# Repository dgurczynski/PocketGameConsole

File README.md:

# PocketGameConsole (ESP32-C3)

Przenośna mini-konsola oparta na układzie **ESP32-C3** z wyświetlaczem OLED 0.96". 

## O projekcie
To mój **pierwszy w życiu projekt PCB**, wykonany w całości w programie KiCad. Skupiłem się w nim na:
* Sprzętowym debouncingu przycisków (filtr RC).
* Czytelnym opisie warstw (Silkscreen) i estetyce logotypu.
* Bezpiecznym zasilaniu bateryjnym (dioda Schottky'ego).

## Zawartość repozytorium
* **[Software](src/):** Kod źródłowy C++ (PlatformIO).
* **[Schemat PDF](hardware/PocketGameConsole.pdf):** Pełna dokumentacja ideowa.
* **[Gerber ZIP](hardware/gerbers/PocketGameConsole_Gerbers.zip):** Pliki gotowe do zamówienia w fabryce.
* **[Projekt KiCad](hardware/pcb_project/):** Pliki źródłowe płytki.

### Podgląd 3D

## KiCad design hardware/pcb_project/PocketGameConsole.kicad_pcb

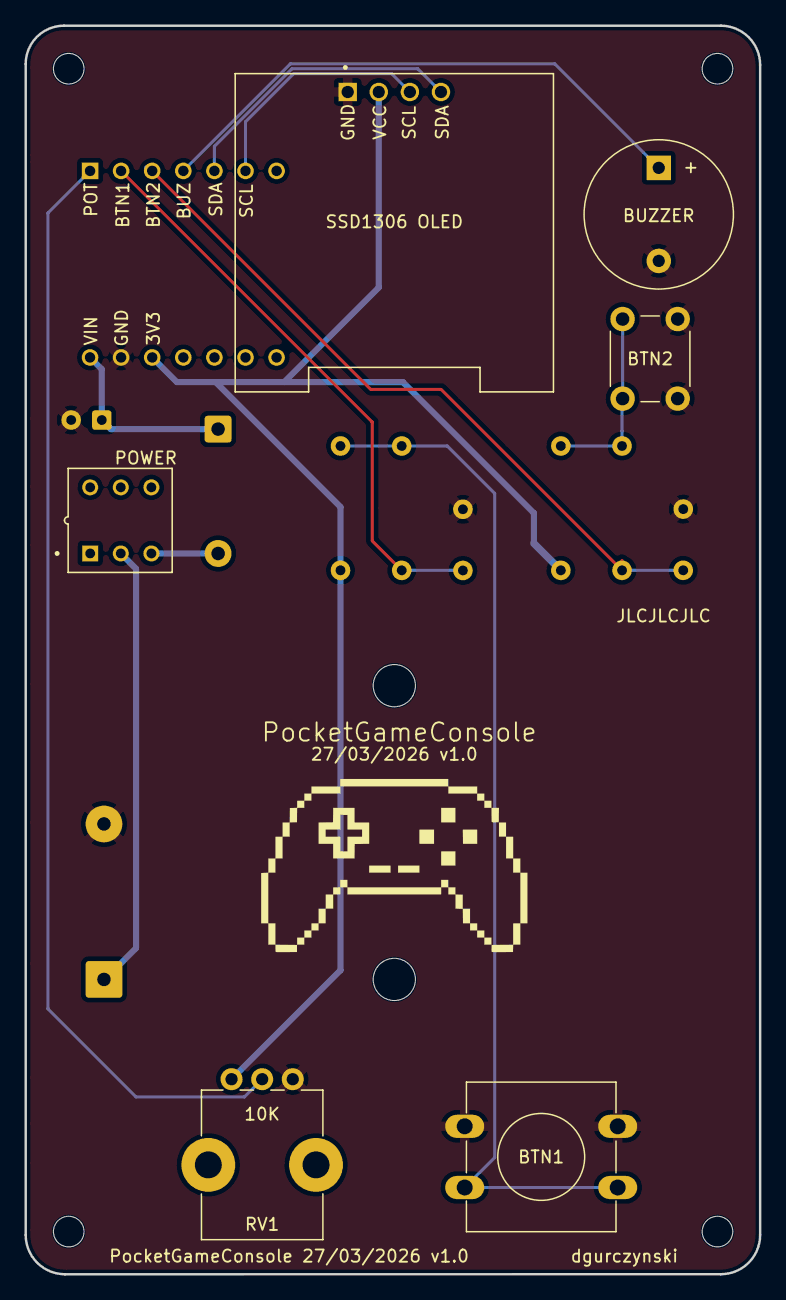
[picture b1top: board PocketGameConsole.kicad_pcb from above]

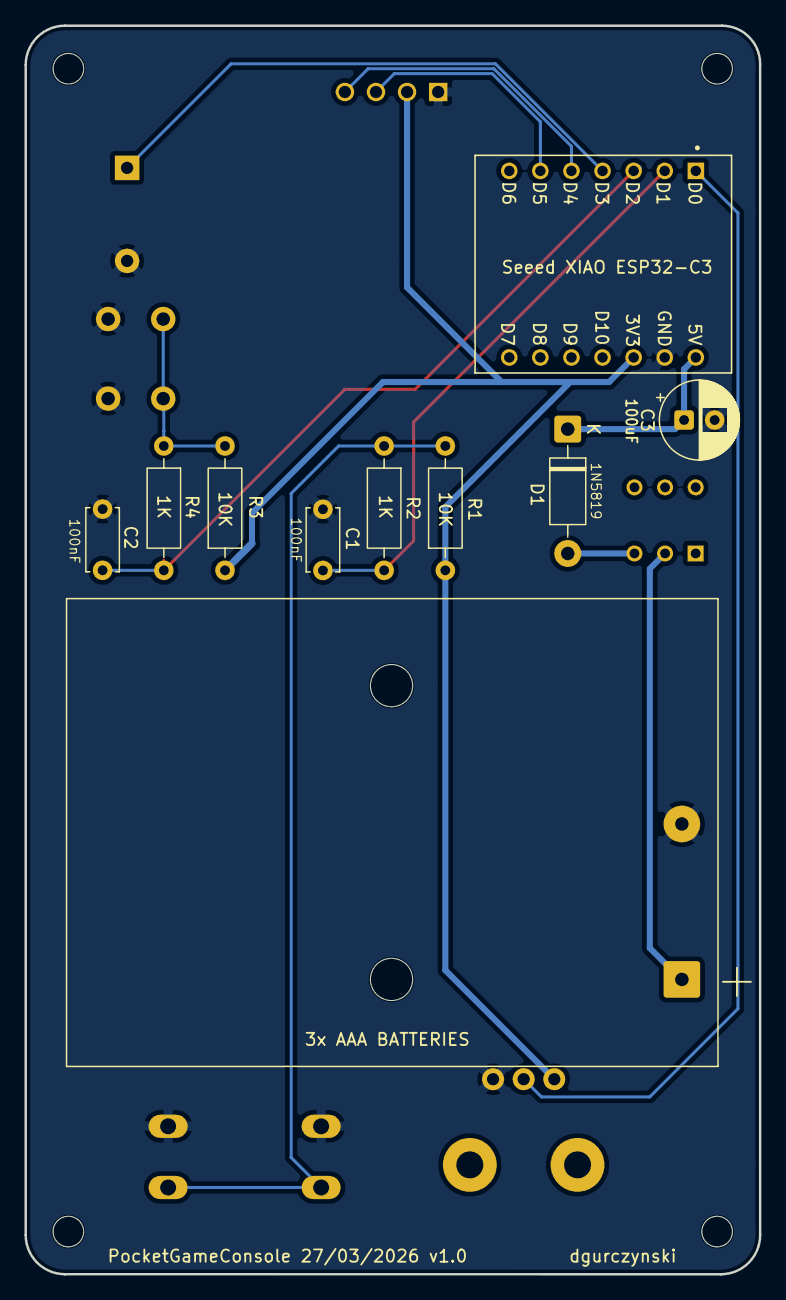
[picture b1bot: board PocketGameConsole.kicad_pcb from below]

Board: 4 copper layers, 60.0 x 102.0 mm, 16 parts (10 on the bottom side), 13 nets.

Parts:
1N5819: 1N5819; D_DO-41_SOD81_P10.16mm_Horizontal
3x AAA BATTERIES: 4.5V; BatteryHolder_Keystone_2479_3xAAA
100nF, 100nF#2: 100nF; C_Disc_D5.0mm_W2.5mm_P5.00mm
BZ1: BUZZER; Buzzer_12x9.5RM7.6
C3: 100uF; CP_Radial_D6.3mm_P2.50mm
R1, R3: 10K; R_Axial_DIN0207_L6.3mm_D2.5mm_P10.16mm_Horizontal
R2, R4: 1K; R_Axial_DIN0207_L6.3mm_D2.5mm_P10.16mm_Horizontal
RV1: 10K; Potentiometer_Bourns_PTV09A-1_Single_Vertical
S1: TL2201EEYA; SW_TL2201EEYA
SSD1306 0.96 OLED: DM-OLED096-636; MODULE_DM-OLED096-636
SW1: SW_Push; SW_PUSH-12mm
SW3: POWER; SW_PUSH_6mm
U1: XIAO-ESP32-C3-DIP; MODULE_XIAO_ESP32C3

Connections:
+3V3: R1.1, R3.1, RV1.1, SSD1306 0.96 OLED.2 (VCC_IN), U1.12 (3V3)
BTN1: 100nF#2.1, R2.2, U1.2 (GPIO3_A1_D1)
BTN2: 100nF.1, R4.2, U1.3 (GPIO4_A2_D2)
BUZ: BZ1.1 (+), U1.4 (GPIO5_A3_D3)
GND: 3x AAA BATTERIES.2 (-), 100nF.2, 100nF#2.2, BZ1.2 (-), C3.2, RV1.3, SSD1306 0.96 OLED.1 (GND), SW1.1, SW3.1, U1.13 (GND)
unnamed: 3x AAA BATTERIES.1 (+), S1.2
unnamed: 1N5819.2 (A), S1.3
unnamed: R1.2, R2.1, SW1.2
unnamed: R3.2, R4.1, SW3.2
POT: RV1.2, U1.1 (GPIO2_A0_D0)
SCL: SSD1306 0.96 OLED.3 (SCL), U1.6 (GPIO7_D5_SCL)
SDA: SSD1306 0.96 OLED.4 (SDA), U1.5 (GPIO6_D4_SDA)
VCC_BAT: 1N5819.1 (K), C3.1, U1.14 (VBUS)

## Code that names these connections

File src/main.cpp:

#include <Arduino.h>
#include <math.h>
#include <Wire.h>
#include <Adafruit_GFX.h>
#include <Adafruit_SSD1306.h>

#include "Menu.h"

#define SCREEN_WIDTH 128
#define SCREEN_HEIGHT 64

#define PIN_POT 2
#define PIN_BTN1 3
#define PIN_BTN2 4
#define PIN_BUZZ 5

Adafruit_SSD1306 display(SCREEN_WIDTH, SCREEN_HEIGHT, &Wire, -1);

Menu menu;

void setup() {
  Serial.begin(115200);
  Wire.begin();
  
  pinMode(PIN_BUZZ, OUTPUT);
  pinMode(PIN_BTN1, INPUT_PULLUP);
  pinMode(PIN_BTN2, INPUT_PULLUP);

  display.begin(SSD1306_SWITCHCAPVCC, 0x3C);
  menu.init(PIN_BTN1, PIN_BTN2, PIN_POT, PIN_BUZZ, SCREEN_WIDTH, SCREEN_HEIGHT);

  randomSeed(esp_random());
}

void loop() {
  menu.update();
}
